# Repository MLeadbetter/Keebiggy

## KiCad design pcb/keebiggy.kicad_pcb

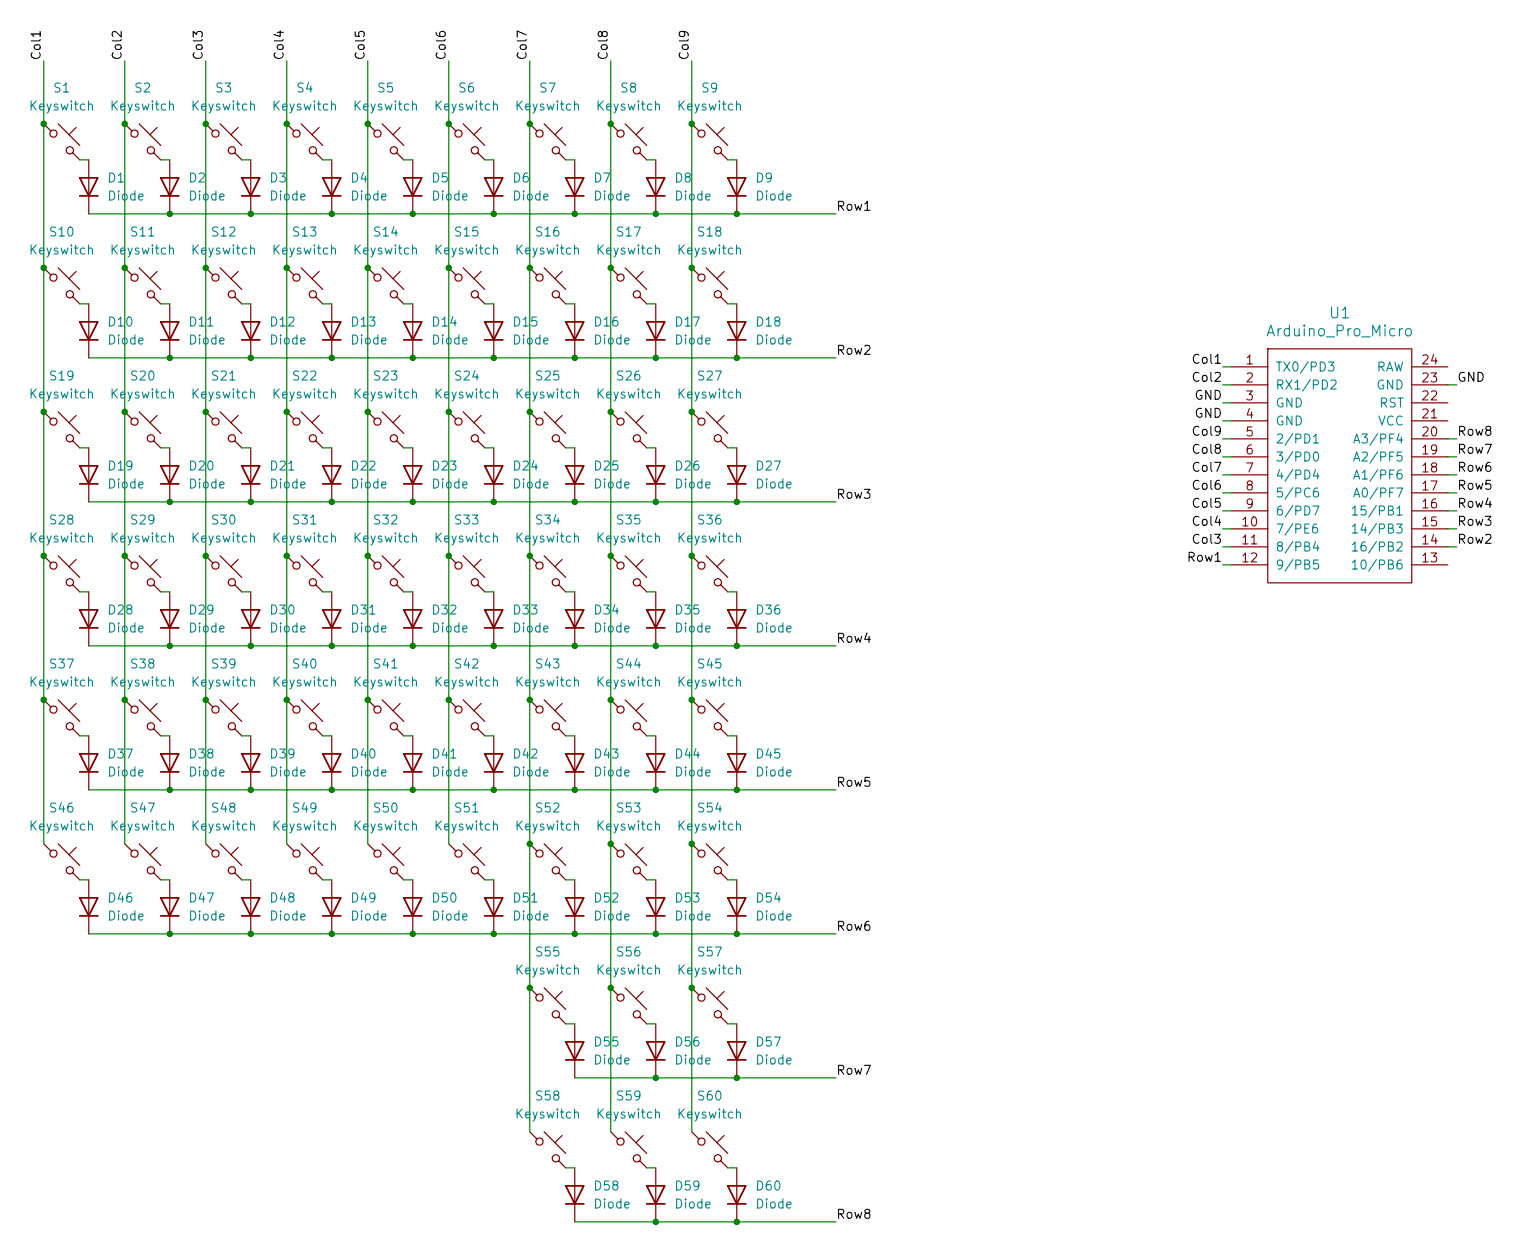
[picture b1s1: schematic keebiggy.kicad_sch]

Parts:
D1, D2, D3, D4, D5, D6, D7, D8, D9, D10, D11, D12, D13, D14, D15, D16, D17, D18, D19, D20, D21, D22, D23, D24, D25, D26, D27, D28, D29, D30, D31, D32, D33, D34, D35, D36, D37, D38, D39, D40, D41, D42, D43, D44, D45, D46, D47, D48, D49, D50, D51, D52, D53, D54, D55, D56, D57, D58, D59, D60: Diode; Diode_DO-35
S1, S2, S3, S4, S5, S6, S7, S8, S9, S10, S11, S12, S13, S14, S15, S16, S17, S18, S19, S20, S21, S22, S23, S24, S25, S26, S27, S28, S29, S30, S31, S32, S33, S34, S35, S36, S37, S38, S39, S40, S41, S42, S43, S44, S45, S46, S47, S48, S49, S50, S51, S52, S53, S54, S55, S56, S57, S58, S59, S60: Keyswitch; MX_PCB_1.00u
U1: Arduino_Pro_Micro

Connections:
/Col1: S1.1, S10.1, S19.1, S28.1, S37.1, S46.1, U1.1 (TX0/PD3)
/Col2: S2.1, S11.1, S20.1, S29.1, S38.1, S47.1, U1.2 (RX1/PD2)
/Col3: S3.1, S12.1, S21.1, S30.1, S39.1, S48.1, U1.11 (8/PB4)
/Col4: S4.1, S13.1, S22.1, S31.1, S40.1, S49.1, U1.10 (7/PE6)
/Col5: S5.1, S14.1, S23.1, S32.1, S41.1, S50.1, U1.9 (6/PD7)
/Col6: S6.1, S15.1, S24.1, S33.1, S42.1, S51.1, U1.8 (5/PC6)
/Col7: S7.1, S16.1, S25.1, S34.1, S43.1, S52.1, S55.1, S58.1, U1.7 (4/PD4)
/Col8: S8.1, S17.1, S26.1, S35.1, S44.1, S53.1, S56.1, S59.1, U1.6 (3/PD0)
/Col9: S9.1, S18.1, S27.1, S36.1, S45.1, S54.1, S57.1, S60.1, U1.5 (2/PD1)
/GND: U1.3 (GND), U1.4 (GND), U1.23 (GND)
/Row1: D1.1 (K), D2.1 (K), D3.1 (K), D4.1 (K), D5.1 (K), D6.1 (K), D7.1 (K), D8.1 (K), D9.1 (K), U1.12 (9/PB5)
/Row2: D10.1 (K), D11.1 (K), D12.1 (K), D13.1 (K), D14.1 (K), D15.1 (K), D16.1 (K), D17.1 (K), D18.1 (K), U1.14 (16/PB2)
/Row3: D19.1 (K), D20.1 (K), D21.1 (K), D22.1 (K), D23.1 (K), D24.1 (K), D25.1 (K), D26.1 (K), D27.1 (K), U1.15 (14/PB3)
/Row4: D28.1 (K), D29.1 (K), D30.1 (K), D31.1 (K), D32.1 (K), D33.1 (K), D34.1 (K), D35.1 (K), D36.1 (K), U1.16 (15/PB1)
/Row5: D37.1 (K), D38.1 (K), D39.1 (K), D40.1 (K), D41.1 (K), D42.1 (K), D43.1 (K), D44.1 (K), D45.1 (K), U1.17 (A0/PF7)
/Row6: D46.1 (K), D47.1 (K), D48.1 (K), D49.1 (K), D50.1 (K), D51.1 (K), D52.1 (K), D53.1 (K), D54.1 (K), U1.18 (A1/PF6)
/Row7: D55.1 (K), D56.1 (K), D57.1 (K), U1.19 (A2/PF5)
/Row8: D58.1 (K), D59.1 (K), D60.1 (K), U1.20 (A3/PF4)
unnamed: D1.2 (A), S1.2
unnamed: D2.2 (A), S2.2
unnamed: D3.2 (A), S3.2
unnamed: D4.2 (A), S4.2
unnamed: D5.2 (A), S5.2
unnamed: D6.2 (A), S6.2
unnamed: D7.2 (A), S7.2
unnamed: D8.2 (A), S8.2
unnamed: D9.2 (A), S9.2
unnamed: D10.2 (A), S10.2
unnamed: D11.2 (A), S11.2
unnamed: D12.2 (A), S12.2
unnamed: D13.2 (A), S13.2
unnamed: D14.2 (A), S14.2
unnamed: D15.2 (A), S15.2
unnamed: D16.2 (A), S16.2
unnamed: D17.2 (A), S17.2
unnamed: D18.2 (A), S18.2
unnamed: D19.2 (A), S19.2
unnamed: D20.2 (A), S20.2
unnamed: D21.2 (A), S21.2
unnamed: D22.2 (A), S22.2
unnamed: D23.2 (A), S23.2
unnamed: D24.2 (A), S24.2
unnamed: D25.2 (A), S25.2
unnamed: D26.2 (A), S26.2
unnamed: D27.2 (A), S27.2
unnamed: D28.2 (A), S28.2
unnamed: D29.2 (A), S29.2
unnamed: D30.2 (A), S30.2
unnamed: D31.2 (A), S31.2
unnamed: D32.2 (A), S32.2
unnamed: D33.2 (A), S33.2
unnamed: D34.2 (A), S34.2
unnamed: D35.2 (A), S35.2
unnamed: D36.2 (A), S36.2
unnamed: D37.2 (A), S37.2
unnamed: D38.2 (A), S38.2
unnamed: D39.2 (A), S39.2
unnamed: D40.2 (A), S40.2
unnamed: D41.2 (A), S41.2
unnamed: D42.2 (A), S42.2
unnamed: D43.2 (A), S43.2
unnamed: D44.2 (A), S44.2
unnamed: D45.2 (A), S45.2
unnamed: D46.2 (A), S46.2
unnamed: D47.2 (A), S47.2
unnamed: D48.2 (A), S48.2
unnamed: D49.2 (A), S49.2
unnamed: D50.2 (A), S50.2
unnamed: D51.2 (A), S51.2
unnamed: D52.2 (A), S52.2
unnamed: D53.2 (A), S53.2
unnamed: D54.2 (A), S54.2
unnamed: D55.2 (A), S55.2
unnamed: D56.2 (A), S56.2
unnamed: D57.2 (A), S57.2
unnamed: D58.2 (A), S58.2
unnamed: D59.2 (A), S59.2
unnamed: D60.2 (A), S60.2

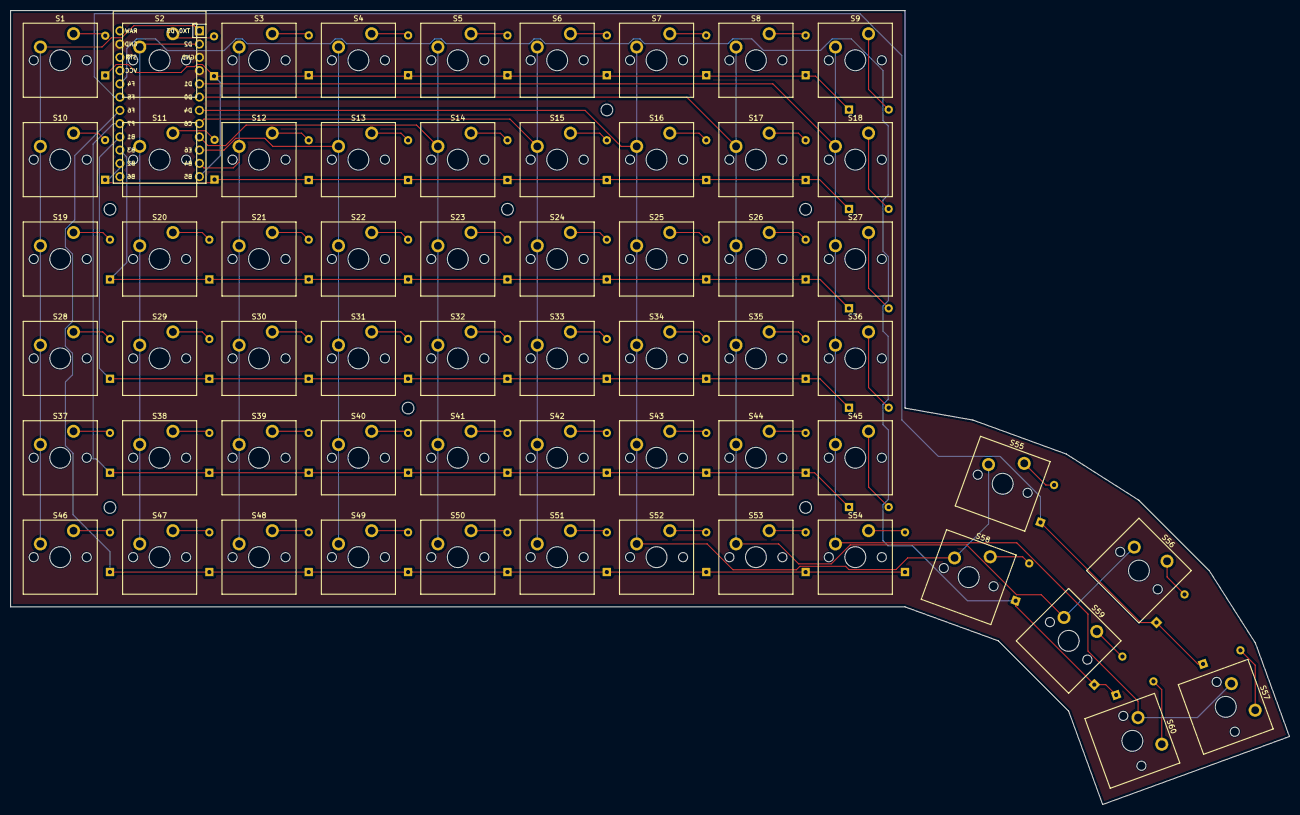
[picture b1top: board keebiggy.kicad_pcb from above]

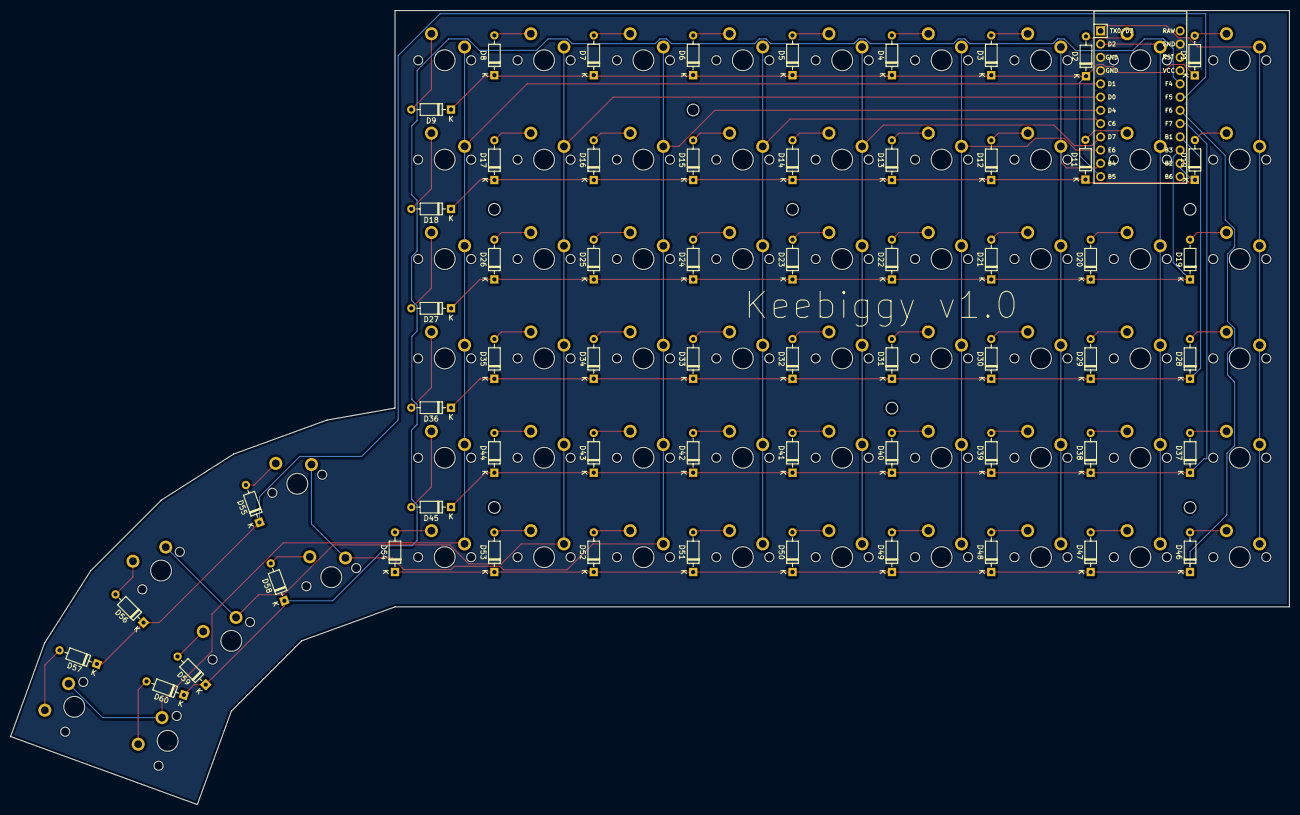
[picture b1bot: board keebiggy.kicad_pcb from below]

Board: 2 copper layers, 245.1 x 152.2 mm, 121 parts (61 on the bottom side), 78 nets.

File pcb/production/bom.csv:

Designator,Footprint,Quantity,Value,LCSC Part #
"D1, D10, D11, D12, D13, D14, D15, D16, D17, D18, D19, D2, D20, D21, D22, D23, D24, D25, D26, D27, D28, D29, D3, D30, D31, D32, D33, D34, D35, D36, D37, D38, D39, D4, D40, D41, D42, D43, D44, D45, D46, D47, D48, D49, D5, D50, D51, D52, D53, D54, D55, D56, D57, D58, D59, D6, D60, D7, D8, D9",Diode_DO-35,60,Diode,
"S1, S10, S11, S12, S13, S14, S15, S16, S17, S18, S19, S2, S20, S21, S22, S23, S24, S25, S26, S27, S28, S29, S3, S30, S31, S32, S33, S34, S35, S36, S37, S38, S39, S4, S40, S41, S42, S43, S44, S45, S46, S47, S48, S49, S5, S50, S51, S52, S53, S54, S55, S56, S57, S58, S59, S6, S60, S7, S8, S9",MX_PCB_1.00u,60,Keyswitch,
U1,Arduino_Pro_Micro,1,Arduino_Pro_Micro,
